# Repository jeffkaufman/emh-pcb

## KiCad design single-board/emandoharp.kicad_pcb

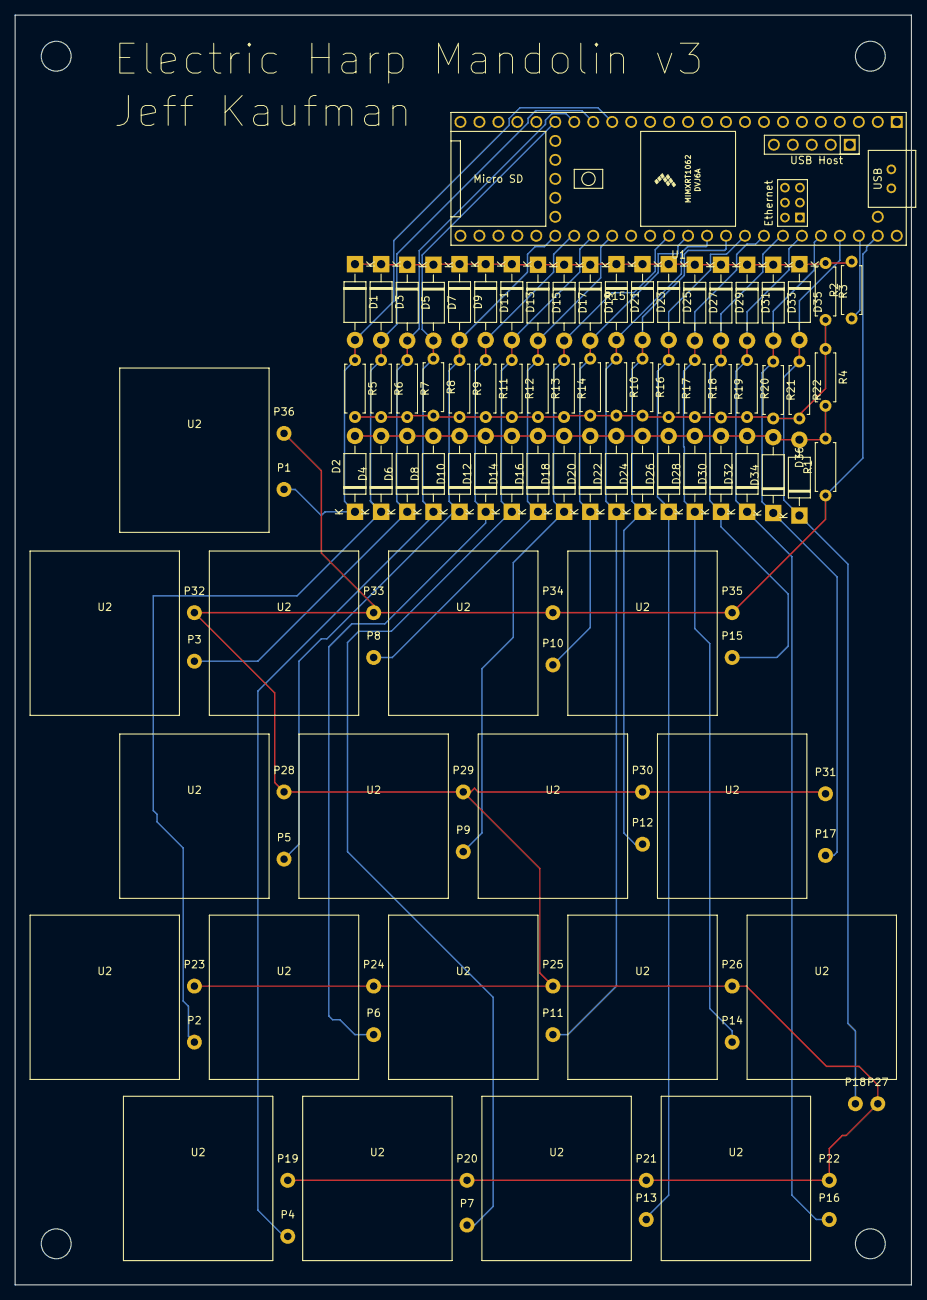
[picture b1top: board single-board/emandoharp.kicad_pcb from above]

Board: 2 copper layers, 120.0 x 170.0 mm, 113 parts (0 on the bottom side), 23 nets.

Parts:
D1, D2, D3, D4, D5, D6, D7, D8, D9, D10, D11, D12, D13, D14, D15, D16, D17, D18, D19, D20, D21, D22, D23, D24, D25, D26, D27, D28, D29, D30, D31, D32, D33, D34, D35, D36: 1N5819; D_DO-41_SOD81_P10.16mm_Horizontal
P1, P2, P3, P4, P5, P6, P7, P8, P9, P10, P11, P12, P13, P14, P15, P16, P17, P18: piezo; MountingHole_0.5mm_M2_DIN965_Pad
P19, P20, P21, P22, P23, P24, P25, P26, P27, P28, P29, P30, P31, P32, P33, P34, P35, P36: gnd; MountingHole_0.5mm_M2_DIN965_Pad
R1, R2, R3, R4: 10kΩ; R_Axial_DIN0207_L6.3mm_D2.5mm_P7.62mm_Horizontal
R5, R6, R7, R8, R9, R10, R11, R12, R13, R14, R15, R16, R17, R18, R19, R20, R21, R22: 1MΩ; R_Axial_DIN0207_L6.3mm_D2.5mm_P7.62mm_Horizontal
U1: Teensy4.1; Teensy41
U2, U2#2, U2#3, U2#4, U2#5, U2#6, U2#7, U2#8, U2#9, U2#10, U2#11, U2#12, U2#13, U2#14, U2#15, U2#16, U2#17, U2#18: Knowles_LGA-6_4.72x3.76mm

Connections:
unnamed: D1.2 (A), D2.1 (K), P1.1, R5.1, U1.16 (24_A10_TX6_SCL2)
unnamed: D1.1 (K), D3.1 (K), D5.1 (K), D7.1 (K), D9.1 (K), D11.1 (K), D13.1 (K), D15.1 (K), D17.1 (K), D19.1 (K), D21.1 (K), D23.1 (K), D25.1 (K), D27.1 (K), D29.1 (K), D31.1 (K), D33.1 (K), D35.1 (K), R2.2, R3.1
unnamed: D3.2 (A), D4.1 (K), P2.1, R6.1, U1.17 (25_A11_RX6_SDA2)
unnamed: D5.2 (A), D6.1 (K), P3.1, R7.1, U1.18 (26_A12_MOSI1)
unnamed: D7.2 (A), D8.1 (K), P4.1, R8.1, U1.19 (27_A13_SCK1)
unnamed: D2.2 (A), D4.2 (A), D6.2 (A), D8.2 (A), D10.2 (A), D12.2 (A), D14.2 (A), D16.2 (A), D18.2 (A), D20.2 (A), D22.2 (A), D24.2 (A), D26.2 (A), D28.2 (A), D30.2 (A), D32.2 (A), D34.2 (A), D36.2 (A), R1.2, R4.2
unnamed: D9.2 (A), D10.1 (K), P5.1, R9.1, U1.30 (38_CS1_IN1)
unnamed: D11.2 (A), D12.1 (K), P6.1, R11.1, U1.31 (39_MISO1_OUT1A)
unnamed: D13.2 (A), D14.1 (K), P7.1, R12.1, U1.32 (40_A16)
unnamed: D15.2 (A), D16.1 (K), P8.1, R13.1, U1.33 (41_A17)
unnamed: D17.2 (A), D18.1 (K), P9.1, R14.1, U1.36 (14_A0_TX3_SPDIF_OUT)
unnamed: D19.2 (A), D20.1 (K), P10.1, R15.1, U1.37 (15_A1_RX3_SPDIF_IN)
unnamed: D21.2 (A), D22.1 (K), P11.1, R10.1, U1.38 (16_A2_RX4_SCL1)
unnamed: D23.2 (A), D24.1 (K), P12.1, R16.1, U1.39 (17_A3_TX4_SDA1)
unnamed: D25.2 (A), D26.1 (K), P13.1, R17.1, U1.40 (18_A4_SDA)
unnamed: D27.2 (A), D28.1 (K), P14.1, R18.1, U1.41 (19_A5_SCL)
unnamed: D29.2 (A), D30.1 (K), P15.1, R19.1, U1.42 (20_A6_TX5_LRCLK1)
unnamed: D31.2 (A), D32.1 (K), P16.1, R20.1, U1.43 (21_A7_RX5_BCLK1)
unnamed: D33.2 (A), D34.1 (K), P17.1, R21.1, U1.44 (22_A8_CTX1)
unnamed: D35.2 (A), D36.1 (K), P18.1, R22.1, U1.45 (23_A9_CRX1_MCLK1)
unnamed: P19.1, P20.1, P21.1, P22.1, P23.1, P24.1, P25.1, P26.1, P27.1, P28.1, P29.1, P30.1, P31.1, P32.1, P33.1, P34.1, P35.1, P36.1, R1.1, U1.47 (GND)
unnamed: R2.1, U1.46 (3V3)
unnamed: R3.2, R4.1, R5.2, R6.2, R7.2, R8.2, R9.2, R10.2, R11.2, R12.2, R13.2, R14.2, R15.2, R16.2, R17.2, R18.2, R19.2, R20.2, R21.2, R22.2

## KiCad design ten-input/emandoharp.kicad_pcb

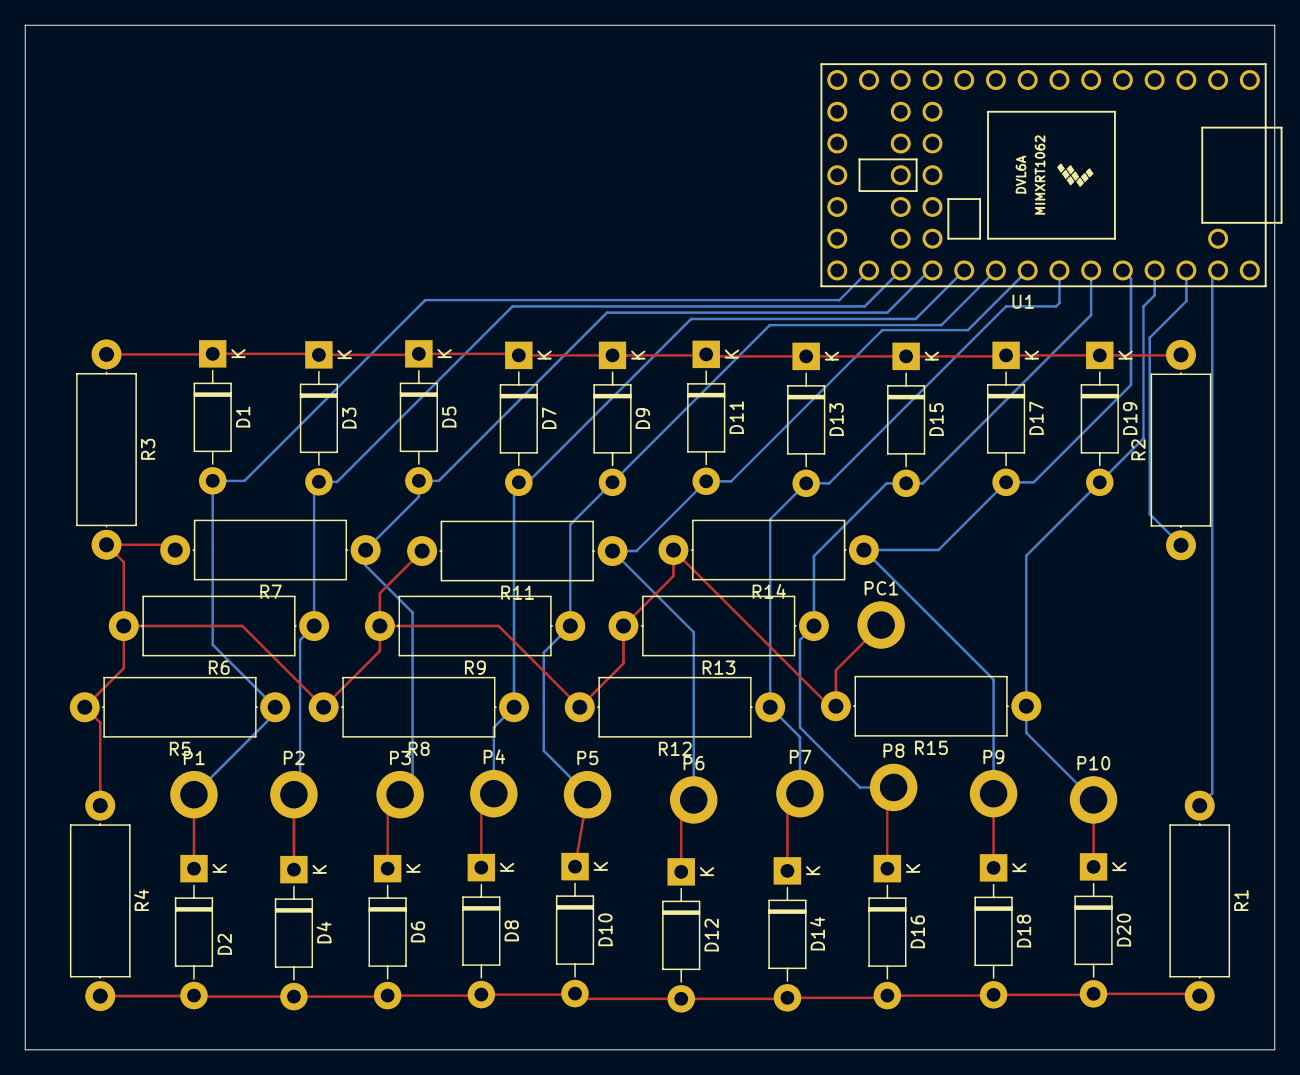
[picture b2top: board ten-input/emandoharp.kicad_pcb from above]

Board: 2 copper layers, 100.0 x 82.0 mm, 46 parts (0 on the bottom side), 15 nets.

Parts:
D1, D2, D3, D4, D5, D6, D7, D8, D9, D10, D11, D12, D13, D14, D15, D16, D17, D18, D19, D20: 1N5819; D_DO-41_SOD81_P10.16mm_Horizontal
P1, P2, P3, P4, P5, P6, P7, P8, P9, P10: piezo; MountingHole_2.2mm_M2_DIN965_Pad
PC1: piezo ground; MountingHole_2.2mm_M2_DIN965_Pad
R1, R2, R3, R4: 10kΩ; R_Axial_DIN0414_L11.9mm_D4.5mm_P15.24mm_Horizontal
R5, R6, R7, R8, R9, R11, R12, R13, R14, R15: 1MΩ; R_Axial_DIN0414_L11.9mm_D4.5mm_P15.24mm_Horizontal
U1: Teensy4.0; Teensy40

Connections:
unnamed: D1.2 (A), D2.1 (K), P1.1, R5.1, U1.21 (14_A0_TX3_SPDIF_OUT)
unnamed: D1.1 (K), D3.1 (K), D5.1 (K), D7.1 (K), D9.1 (K), D11.1 (K), D13.1 (K), D15.1 (K), D17.1 (K), D19.1 (K), R2.2, R3.1
unnamed: D3.2 (A), D4.1 (K), P2.1, R6.1, U1.22 (15_A1_RX3_SPDIF_IN)
unnamed: D5.2 (A), D6.1 (K), P3.1, R7.1, U1.23 (16_A2_RX4_SCL1)
unnamed: D7.2 (A), D8.1 (K), P4.1, R8.1, U1.24 (17_A3_TX4_SDA1)
unnamed: D2.2 (A), D4.2 (A), D6.2 (A), D8.2 (A), D10.2 (A), D12.2 (A), D14.2 (A), D16.2 (A), D18.2 (A), D20.2 (A), R1.2, R4.2
unnamed: D9.2 (A), D10.1 (K), P5.1, R9.1, U1.25 (18_A4_SDA0)
unnamed: D11.2 (A), D12.1 (K), P6.1, R11.1, U1.26 (19_A5_SCL0)
unnamed: D13.2 (A), D14.1 (K), P7.1, R12.1, U1.27 (20_A6_TX5_LRCLK1)
unnamed: D15.2 (A), D16.1 (K), P8.1, R13.1, U1.28 (21_A7_RX5_BCLK1)
unnamed: D17.2 (A), D18.1 (K), P9.1, R14.1, U1.29 (22_A8_CTX1)
unnamed: D19.2 (A), D20.1 (K), P10.1, R15.1, U1.30 (23_A9_CRX1_MCLK1)
unnamed: PC1.1, R3.2, R4.1, R5.2, R6.2, R7.2, R8.2, R9.2, R11.2, R12.2, R13.2, R14.2, R15.2
unnamed: R1.1, U1.32 (GND)
unnamed: R2.1, U1.31 (3V3)

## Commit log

2024-04-01 remove errant junction
2024-04-01 move into subdir
2024-04-16 check in 18 input version
2024-04-16 step file
2024-04-16 eighteen input: add box
    Lancelot and I designed a 3D-printable box for the 18-input board.
2024-04-19 add single-board version
2024-04-25 single board: pizeo holes were too small
2024-04-26 whistle synth: check in schematic sketch
2024-05-09 whistle synth pre-amp v1
2026-02-07 starting whistle synth v2
2026-02-07 convert to new kicad format
2026-02-08 check in
2026-02-08 convert audio shield footprint to modern syntax by opening in v8 and then saving
